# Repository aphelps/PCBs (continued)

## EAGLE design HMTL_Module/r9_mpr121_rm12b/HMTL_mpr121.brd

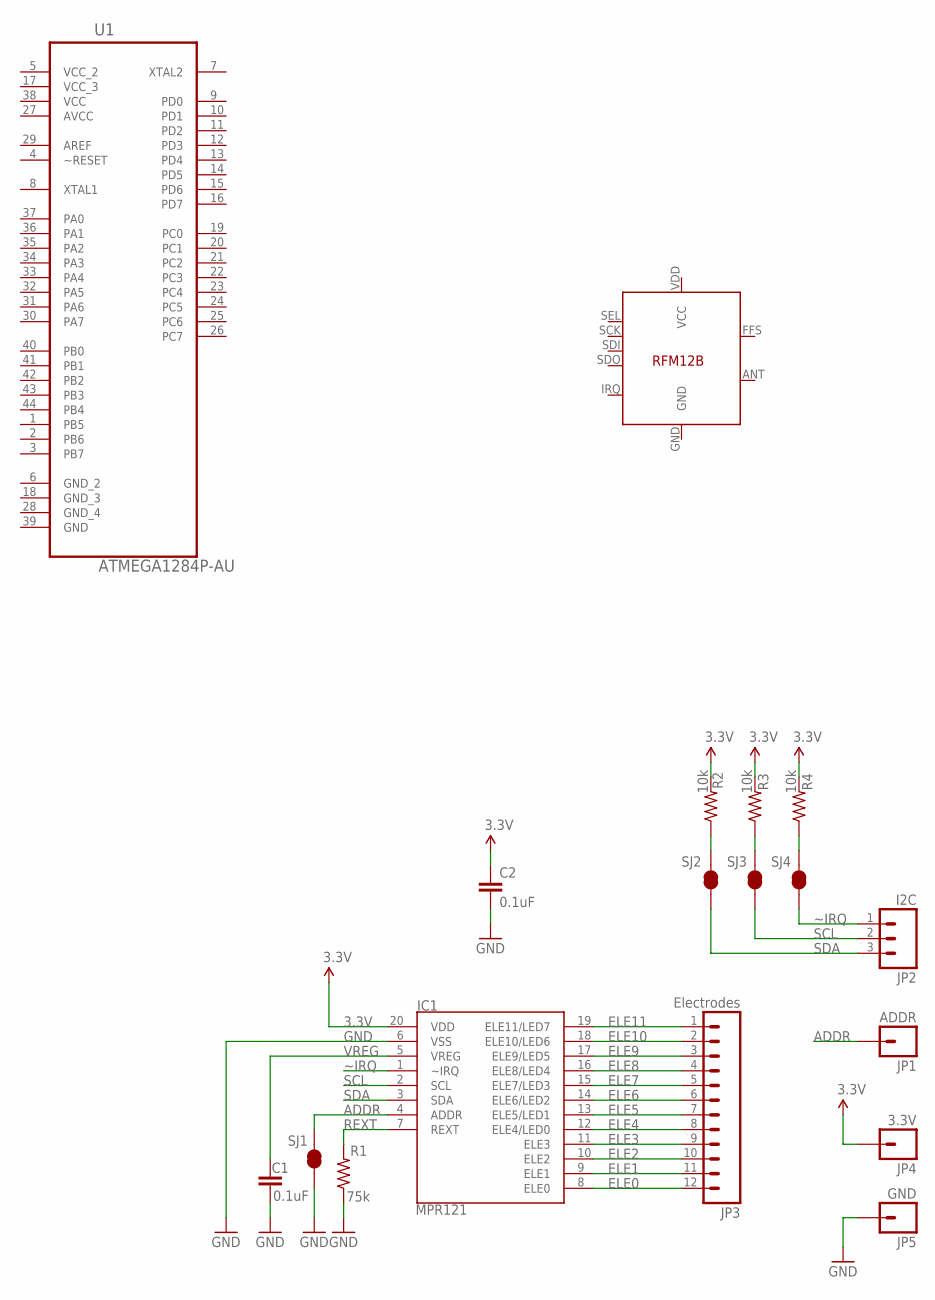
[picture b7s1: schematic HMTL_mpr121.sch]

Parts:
C1, C2: 0.1uF; 0603-CAP
IC1: MPR121; QFN-20-0.4MM-V2
JP1: ADDR; 1X01
JP2: I2C; 1X03
JP3: Electrodes; 1X12
JP4: 3.3V; 1X01
JP5: GND; 1X01
R1: 75k; 0603-RES
R2, R3, R4: 10k; 0603-RES
SJ1, SJ2, SJ3, SJ4: SOLDERJUMPERTRACE; SJ_2S-TRACE
U1: ATMEGA1284P-AU; QFP80P1200X1200X120-44N
U$1: RFM12B

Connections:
3.3V: C2.1, IC1.20 (VDD), JP4.1, R2.2, R3.2, R4.2
ADDR: IC1.4 (ADDR), JP1.1, SJ1.2
AVCC: U1.27 (AVCC)
ELE0: IC1.8 (ELE0), JP3.12
ELE1: IC1.9 (ELE1), JP3.11
ELE2: IC1.10 (ELE2), JP3.10
ELE3: IC1.11 (ELE3), JP3.9
ELE4: IC1.12 (ELE4/LED0), JP3.8
ELE5: IC1.13 (ELE5/LED1), JP3.7
ELE6: IC1.14 (ELE6/LED2), JP3.6
ELE7: IC1.15 (ELE7/LED3), JP3.5
ELE8: IC1.16 (ELE8/LED4), JP3.4
ELE9: IC1.17 (ELE9/LED5), JP3.3
ELE10: IC1.18 (ELE10/LED6), JP3.2
ELE11: IC1.19 (ELE11/LED7), JP3.1
GND: C1.2, C2.2, IC1.6 (VSS), JP5.1, R1.1, SJ1.1, U$1.GND
REXT: IC1.7 (REXT), R1.2
SCL: IC1.2 (SCL), JP2.2, SJ3.1
SCL_PU: R3.1, SJ3.2
SDA: IC1.3 (SDA), JP2.3, SJ2.1
SDA_PU: R2.1, SJ2.2
VCC: U1.38 (VCC), U$1.VDD (VCC)
VCC_2: U1.5 (VCC_2)
VCC_3: U1.17 (VCC_3)
VREG: C1.1, IC1.5 (VREG)
~IRQ: IC1.1 (~IRQ), JP2.1, SJ4.1
~IRQ_PU: R4.1, SJ4.2

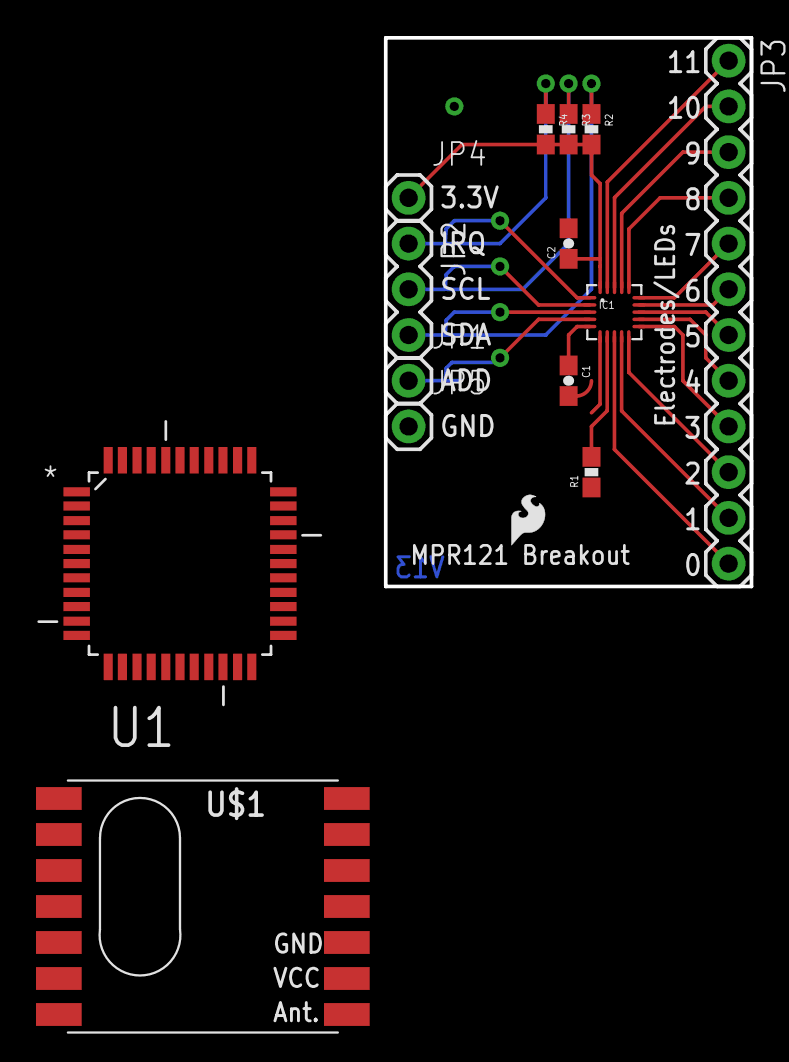
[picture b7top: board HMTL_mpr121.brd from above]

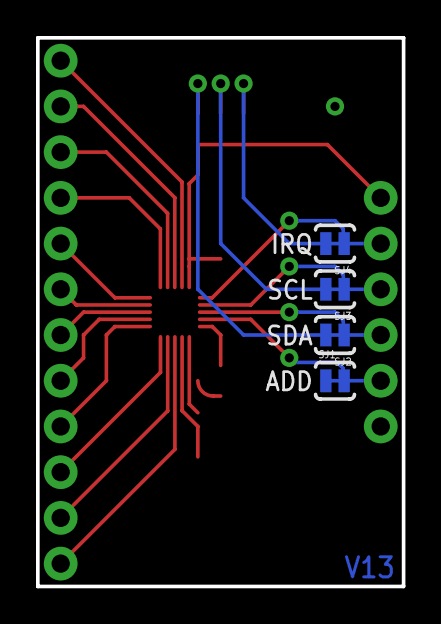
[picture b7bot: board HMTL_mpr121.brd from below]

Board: 2 copper layers, 20.3 x 30.5 mm, 19 parts (4 on the bottom side), 24 nets.

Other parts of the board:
JP6: LOGO-SFESK; SFE-LOGO-FLAME

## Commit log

2017-03-08 Initial working version of a WS2801 based high-power LED driver
2017-03-08 Readme's are important
2017-03-15 Commited older modules
2017-03-15 Additional older modules
2017-04-13 Added license
2017-04-13 Added PDF of scematics for initial high power WS2801 board
2017-04-13 Added PDFs for trigger board
2017-04-13 Removed incomplete module
2017-05-24 Added HMTL board that can take ATMEGA 328 or 1284
2017-05-25 For HTML 328/1284 module added LED for 328
2017-05-25 Added correct 328 plus 1284 layout based on most recent 1284 layout
2017-05-27 Removed incorrect 328 plus 1284 implementation
2017-10-12 2nd iteration of HighPowerWS2801, using SMD IRF510's
2017-10-27 Added initial breakout board for ESP8266 module with FTDI
2017-11-01 Added switch to ESP_FTDI_BREAKOUT
2017-11-10 Added breakout board for connecting ESP to AVR
2017-11-28 Updated ESP8266 module board for connecting to an MCU
2017-11-28 Cleanup
2017-11-29 Initial attempt at a code block for ESP8266 connection to an MCU
2017-12-07 Committing minor change to TriggerBoard_v5
2017-12-08 Initial creation of r10.1 and cleanup
2017-12-12 Added the ESP8266 module to r10.0_328_1284
2017-12-12 Fixed naming error
2017-12-12 Added design block for RFM69HCW
2017-12-22 Finished adding ESP to HMTL r10.1
2018-05-23 Updated the HMTL RFM69 board to fix problems
